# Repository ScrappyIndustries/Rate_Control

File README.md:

### [Nano RC12-3](Nano/RC12-3)
- uses a Nano (with ENC28J60 Ethernet shield) & an on-board mounted Cytron for rate control
	- 1 or 2 [MD13S](https://www.cytron.io/p-13amp-6v-30v-dc-motor-driver) for rate control
- self assembled through-hole board, least expensive
- controls two rates
- can be connected to a relay module with a 20 pin cable or dupont connectors
- work switch
- pressure switch
- [OSHPARK]([https://oshpark.com/shared_projects/UU8e90h9](https://oshpark.com/shared_projects/fRBlR1Se)

#
### [Teensy 4.1 RC11-2](Teensy/RC11-2_PCB)
- uses a Teensy & an on-board mounted Cytron for rate control
	- either (1) [MD13S](https://www.cytron.io/p-13amp-6v-30v-dc-motor-driver) for single rate control
 	- or (1) [MDD10A](https://www.cytron.io/p-10amp-5v-30v-dc-motor-driver-2-channels) for dual rate control
- small components are surface mount parts
- Teensy Ethernet 
- can control two rates and eight sections
	- 8 relays (SPDT 12V output)
	- (1) 5V or 12V analog (pressure) input, potentiometer adjustable filtering
	- (2) optically isolated digital (rate/pulse) inputs (5V or 12V)
- 3.3V I2C headers (Qwiic)
	- supports optional external RelayDriver5 I2C board
 - work switch
 - canbus

#
### [ESP32 RC15](ESP32/RC15)
- uses an ESP32 (optional W5500 Ethernet Module)
- mostly surface mount parts
- can control two rates and 7-14 sections
	- (2) DRV8870 motor drivers with reversible outputs for rates
	- (7) DRV8870 motor drivers for 7 reversible (motorized ball valve) outputs 
- (4) 5V analog inputs (or 2 differential inputs)
- (2) optically isolated digital (rate/pulse) inputs, up to 12V
- RS485 chip & header
- 3.3V I2C header
	- supports optional external RelayDriver5 I2C board

#
### [RelayDriver5](RelayDriver5)
- PCA9535 based I2C IO expander
- designed to plug into 8 or 16 channel relay board with Qwiic cable

#
### Firmware
https://github.com/SK21/AOG_RC

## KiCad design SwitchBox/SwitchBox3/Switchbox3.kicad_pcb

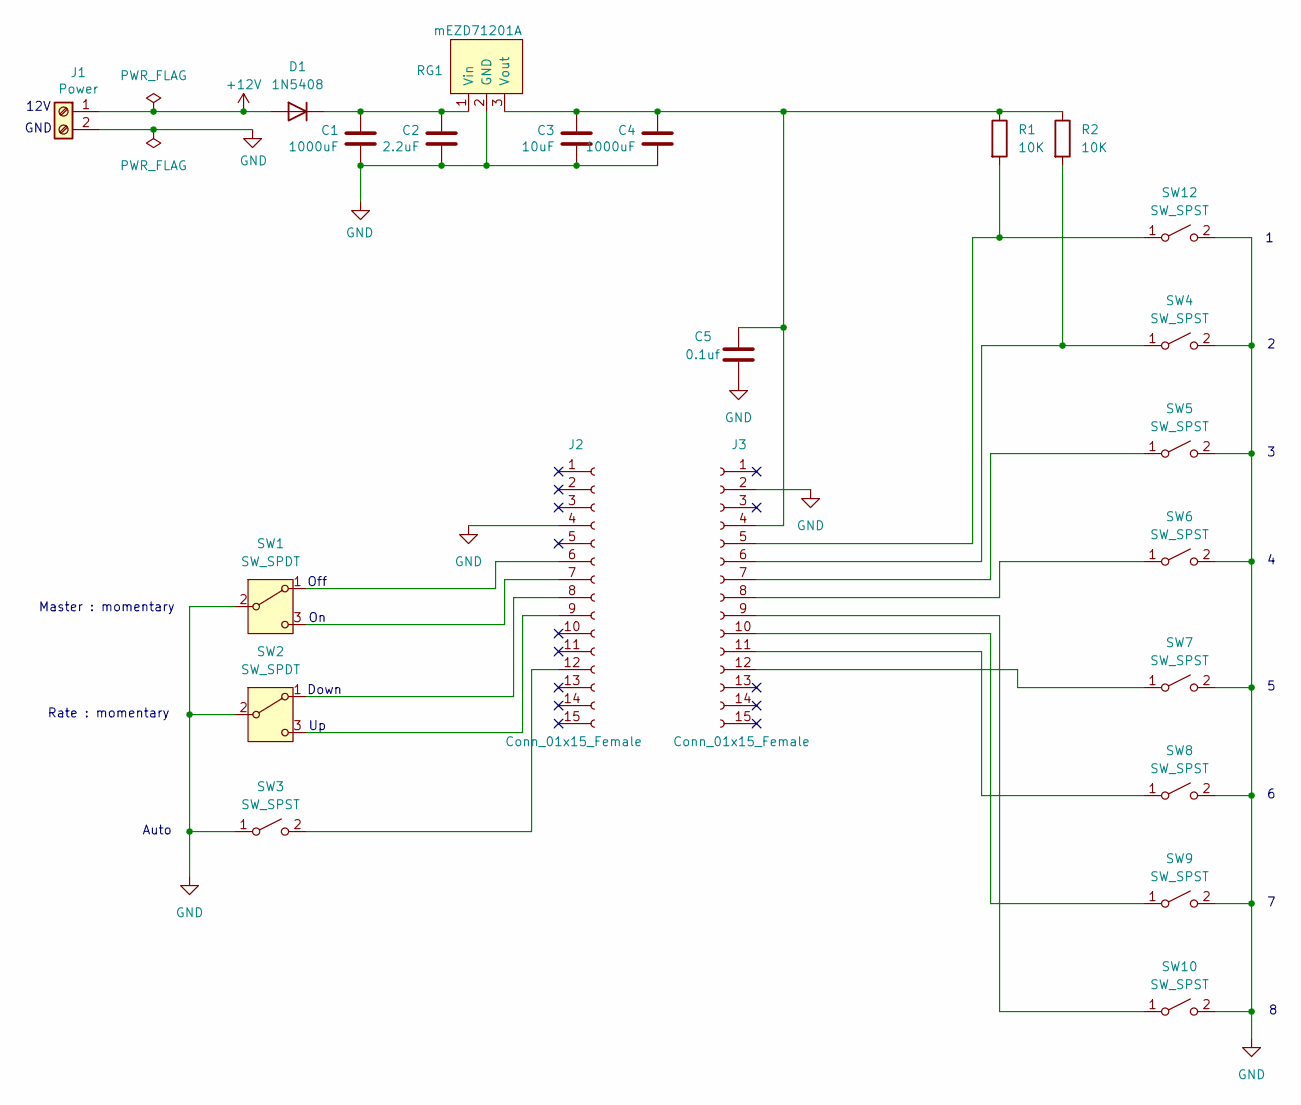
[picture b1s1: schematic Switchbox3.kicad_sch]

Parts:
C1, C4: 1000uF; CP_Radial_D10.0mm_P5.00mm
C2: 2.2uF; C_Disc_D5.0mm_W2.5mm_P2.50mm
C3: 10uF; C_Disc_D5.0mm_W2.5mm_P2.50mm
C5: 0.1uf; C_Disc_D5.0mm_W2.5mm_P2.50mm
D1: 1N5408
J1: Power; TerminalBlock_Phoenix_PT-1,5-2-5.0-H_1x02_P5.00mm_Horizontal
J2, J3: Conn_01x15_Female; PinSocket_1x15_P2.54mm_Vertical
R1, R2: 10K; R_Axial_DIN0207_L6.3mm_D2.5mm_P10.16mm_Horizontal
RG1: mEZD71201A
SW1, SW2: SW_SPDT; Mini_Toggle_3pin
SW3, SW4, SW5, SW6, SW7, SW8, SW9, SW10, SW12: SW_SPST; Mini_Toggle_2pin

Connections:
+12V: D1.2 (A), J1.1
GND: C1.2, C2.2, C3.2, C4.2, C5.1, J1.2, J2.4, J3.2, RG1.2 (GND), SW1.2 (B), SW2.2 (B), SW3.1 (A), SW4.2 (B), SW5.2 (B), SW6.2 (B), SW7.2 (B), SW8.2 (B), SW9.2 (B), SW10.2 (B), SW12.2 (B)
unnamed: C1.1, C2.1, D1.1 (K), RG1.1 (Vin)
unnamed: J2.6, SW1.1 (A)
unnamed: J2.7, SW1.3 (C)
unnamed: J2.8, SW2.1 (A)
unnamed: J2.9, SW2.3 (C)
unnamed: J2.12, SW3.2 (B)
unnamed: C3.1, C4.1, C5.2, J3.4, R1.1, R2.1, RG1.3 (Vout)
unnamed: J3.5, R1.2, SW12.1 (A)
unnamed: J3.6, R2.2, SW4.1 (A)
unnamed: J3.7, SW5.1 (A)
unnamed: J3.8, SW6.1 (A)
unnamed: J3.9, SW10.1 (A)
unnamed: J3.10, SW9.1 (A)
unnamed: J3.11, SW8.1 (A)
unnamed: J3.12, SW7.1 (A)

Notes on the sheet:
Off
Rate : momentary
Down
Master : momentary
12V
Auto
GND

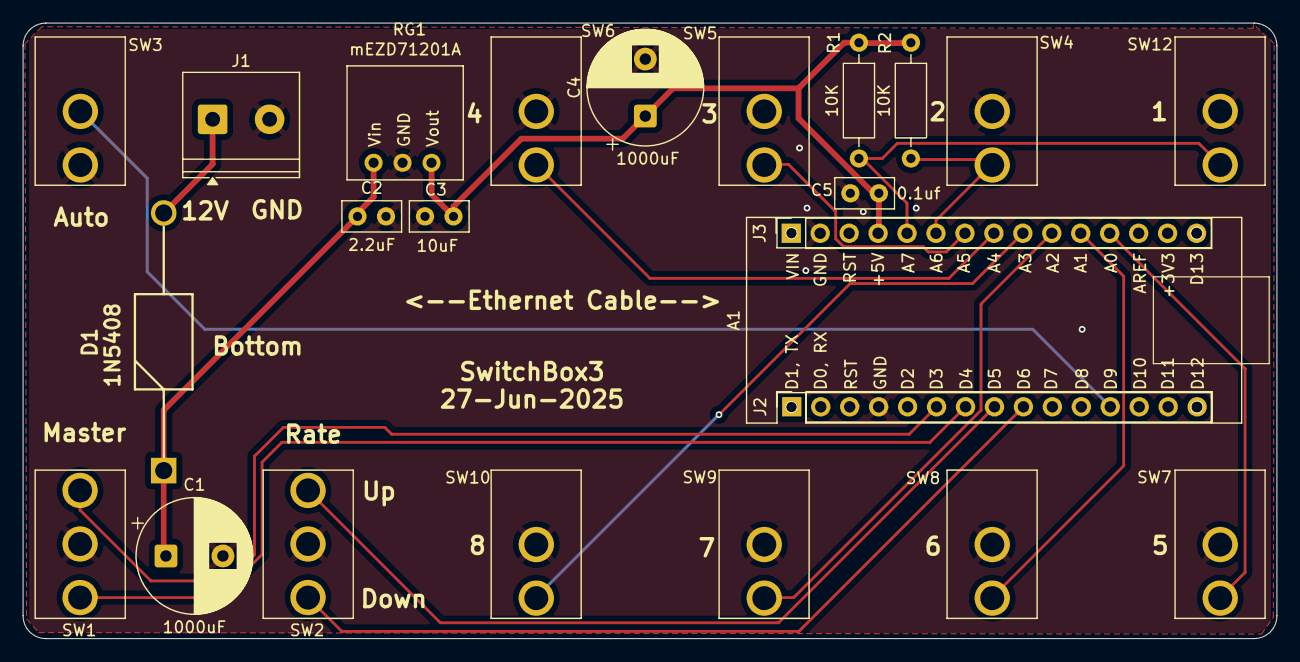
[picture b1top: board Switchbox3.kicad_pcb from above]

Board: 2 copper layers, 110.0 x 54.0 mm, 24 parts (0 on the bottom side), 17 nets.

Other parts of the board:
A1: Arduino_Nano_v3.x; Arduino_Nano_outline

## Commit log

2025-07-06 add Switchbox3
2026-06-19 Create SwitchBox5
2026-06-19 Create SwitchBox5_PCB_01
2026-06-19 Create New
